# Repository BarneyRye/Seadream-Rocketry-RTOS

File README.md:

# Seadream Rocketry PCB and Code
 Kicad files include schematic, pcb, extra symbols, footprints 3d files and also the production files for JLCPCB </br>
 Included code written in Platform.io on VSCode, uses prebuilt libaries and freeRTOS, one task for sensor reading and audio, other task for writing to SD

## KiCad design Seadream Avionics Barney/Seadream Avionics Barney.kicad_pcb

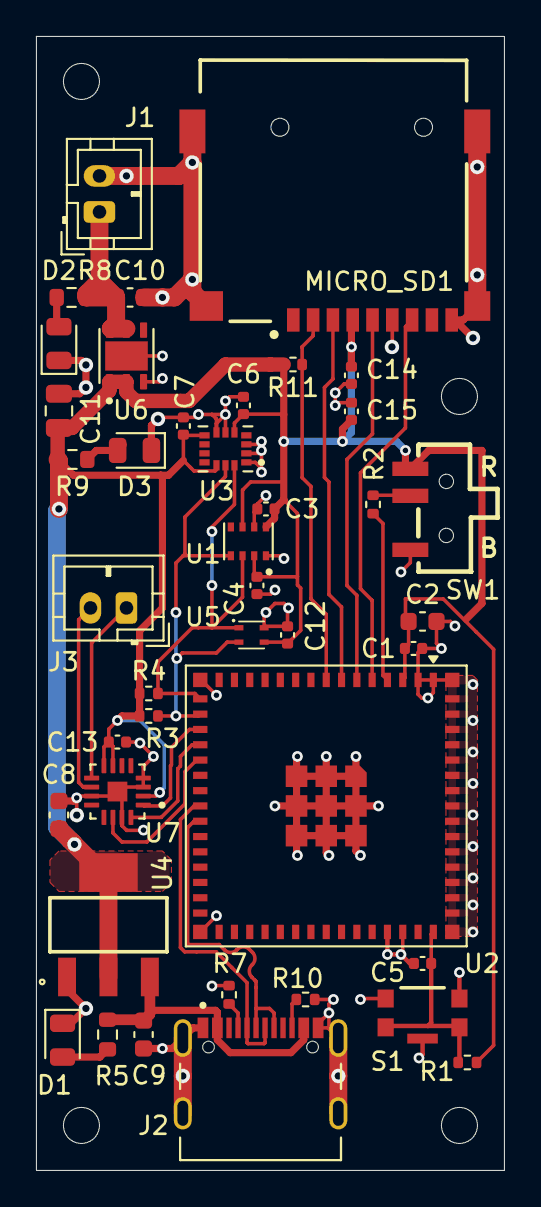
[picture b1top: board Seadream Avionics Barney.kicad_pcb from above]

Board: 2 copper layers, 26.0 x 63.0 mm, 41 parts (0 on the bottom side), 25 nets.

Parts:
C1, C3, C4, C5, C6, C7, C12, C13, C14: 100nF; C_0402_1005Metric
C2, C8, C9, C10: 10uF; C_0603_1608Metric
C11: 22uF; C_0805_2012Metric
C15: 1uF; C_0402_1005Metric
D1, D2, D3: LED; LED_0805_2012Metric
J1, J3: B2B-PH-K-S(LF)(SN); JST_PH_B2B-PH-K_1x02_P2.00mm_Vertical
J2: C393939; SHOUHAN_TYPE-C_16PIN_2MD__073_
MICRO_SD1: C91145; TF-01A
R1, R2, R11: 10k; R_0402_1005Metric
R3, R4: 4k7; R_0402_1005Metric
R5: 330; R_0603_1608Metric
R7, R10: 5k1; R_0402_1005Metric
R8, R9: 220; R_0603_1608Metric
S1: KMR221GLFS; SW_KMR221GLFS
SW1: SSSS810701; SW-SMD_SSSS810701
U1: BMP280; XDCR_BMP280
U2: ESP32-S3-MINI-1U-N8; ESP32-S2-MINI-1U
U3: LSM6DSO32TR; XDCR_LSM6DSO32TR
U4: LD1117S33TR; SOT230P700X180-4N
U5: SHT40-AD1B-R3; SHT4X
U6: LD39200PU33R; SON95P300X300X100-7N
U7: MAX98357AETE_T; QFN50P300X300X80-17N

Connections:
+3.3V: C1.2, C2.2, C3.1, C4.1, C6.1, C7.1, C8.1, C11.2, C12.1, C13.1, C14.2, C15.2, MICRO_SD1.4 (VDD), R1.2, R3.1, R4.1, R9.1, R11.1, SW1.3 (C), U1.2 (CSB), U1.6 (VDDIO), U1.8 (VDD), U2.3 (3V3), U3.5 (VDDIO), U3.8 (VDD), U3.12 (CS), U4.2 (OUT), U4.4 (OUT), U5.3 (VDD), U6.1 (OUT), U6.2 (SENSE), U7.2 (GAIN_SLOT), U7.7 (VDD), U7.8 (VDD)
/BOOT: R2.2, U2.4 (IO0)
/CD: MICRO_SD1.2 (CD/DAT3), R11.2, U2.8 (IO4)
/D+: J2.A6 (DP1), J2.B6 (DP2), U2.24 (IO20)
/D-: J2.A7 (DN1), J2.B7 (DN2), U2.23 (IO19)
/EN: C5.2, R1.1, S1.1, S1.4, U2.45 (EN)
/IO12: R4.2, U1.3 (SDI), U2.16 (IO12), U3.14 (SDA), U5.1 (SDA)
/IO13: R3.2, U1.4 (SCK), U2.17 (IO13), U3.13 (SCL), U5.2 (SCL)
/IO14: U2.18 (IO14), U7.1 (DIN)
/IO15: U2.19 (IO15), U7.16 (BCLK)
/IO16: U2.20 (IO16), U7.14 (LRCLK)
/MISO: MICRO_SD1.7 (DAT0), U2.5 (IO1)
/MOSI: MICRO_SD1.3 (CMD), U2.7 (IO3)
/OUT+: J3.1, U7.9 (OUTP)
/OUT-: J3.2, U7.10 (OUTN)
/SCK: MICRO_SD1.5 (CLK), U2.6 (IO2)
/USB 5V: C9.1, J2.A4_B9 (VBUS_A), J2.B4_A9 (VBUS_B), R5.1, U4.3 (IN)
GND: C1.1, C2.1, C3.2, C4.2, C5.1, C6.2, C7.2, C8.2, C9.2, C10.1, C11.1, C12.2, C13.2, C14.1, C15.1, D1.1 (K), D2.1 (K), D3.1 (K), J1.2, J2.A1_B12 (GND_A), J2.B1_A12 (GND_B), J2.SH1 (SHIELD), J2.SH2 (SHIELD), J2.SH3 (SHIELD), J2.SH4 (SHIELD), MICRO_SD1.6 (VSS), MICRO_SD1.CD1 (CD), MICRO_SD1.MP1 (SHIELD), MICRO_SD1.MP2 (SHIELD), MICRO_SD1.MP3 (SHIELD), MICRO_SD1.MP4 (SHIELD), R7.1, R10.2, S1.2, S1.3, S1.5, SW1.1 (A), U1.1 (GND), U1.7 (GND), U2.1 (GND1), U2.2 (GND1), U2.42 (GND1), U2.43 (GND1), U2.46 (GND1), U2.47 (GND1), U2.48 (GND1), U2.49 (GND1), U2.50 (GND1), U2.51 (GND1), U2.52 (GND1), U2.53 (GND1), U2.54 (GND2), U2.55 (GND2), U2.56 (GND2), U2.57 (GND2), U2.58 (GND2), U2.59 (GND2), U2.60 (GND3), U2.61, U2.62 (GND2), U2.63 (GND2), U2.64 (GND2), U2.65 (GND2), U3.1 (SDO/SA0), U3.2 (SDX), U3.3 (SCX), U3.6 (GND), U3.7 (GND), U4.1 (GND), U5.4 (VSS), U6.3 (GND), U6.7 (EXP), U7.3 (GND), U7.4 (SD_MODE), U7.11 (GND), U7.15 (GND), U7.17 (EP)
unnamed: D1.2 (A), R5.2
unnamed: D2.2 (A), R8.2
unnamed: D3.2 (A), R9.2
unnamed: C10.2, J1.1, R8.1, U6.5 (EN), U6.6 (IN)
unnamed: J2.A5 (CC1), R7.2
unnamed: J2.B5 (CC2), R10.1
unnamed: R2.1, SW1.2 (B)

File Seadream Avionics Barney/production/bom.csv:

"Reference","Qty","Value","DNP","Exclude from BOM","Exclude from Board","Footprint","Datasheet","Description","Part NO."
"C1,C3,C4,C5,C6,C7,C12,C13,C14","9","100nF","","","","Capacitor_SMD:C_0402_1005Metric","https://jlcpcb.com/api/file/downloadByFileSystemAccessId/857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","CL05B104KO5NNNC","C1525"
"C2,C8,C9,C10","4","10uF","","","","Capacitor_SMD:C_0603_1608Metric","https://jlcpcb.com/api/file/downloadByFileSystemAccessId/857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","CL10A106KP8NNNC","C19702"
"C11","1","22uF","","","","Capacitor_SMD:C_0805_2012Metric","https://jlcpcb.com/api/file/downloadByFileSystemAccessId/857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","CL21A226MAQNNNE","C45783"
"C15","1","1uF","","","","Capacitor_SMD:C_0402_1005Metric","https://jlcpcb.com/api/file/downloadByFileSystemAccessId/857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","CL05A105KA5NQNC","C52923"
"D1,D2,D3","3","LED","","","","LED_SMD:LED_0805_2012Metric","https://jlcpcb.com/api/file/downloadByFileSystemAccessId/855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","NCD0805R1","C84256"
"J1,J3","2","B2B-PH-K-S(LF)(SN)","","","","Connector_JST:JST_PH_B2B-PH-K_1x02_P2.00mm_Vertical","https://jlcpcb.com/api/file/downloadByFileSystemAccessId/858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","B2B-PH-K-S(LF)(SN)","C131337"
"J2","1","TYPE-C16PIN","","","","2FOOTPRINTS:SHOUHAN_TYPE-C_16PIN_2MD__073_","https://jlcpcb.com/api/file/downloadByFileSystemAccessId/858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","TYPE-C16PIN","C393939"
"MICRO_SD1","1","TF-01A","","","","2FOOTPRINTS:TF-01A","https://jlcpcb.com/api/file/downloadByFileSystemAccessId/858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","TF-01A","C91145"
"R1,R2,R11","3","10k","","","","Resistor_SMD:R_0402_1005Metric","https://jlcpcb.com/api/file/downloadByFileSystemAccessId/858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","0402WGJ0103TCE","C25531"
"R3,R4","2","4k7","","","","Resistor_SMD:R_0402_1005Metric","https://jlcpcb.com/api/file/downloadByFileSystemAccessId/857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","0402WGF4701TCE","C25900"
"R5","1","330","","","","Resistor_SMD:R_0603_1608Metric","https://jlcpcb.com/api/file/downloadByFileSystemAccessId/857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","0603WAF3300T5E","C23138"
"R7,R10","2","5k1","","","","Resistor_SMD:R_0402_1005Metric","https://jlcpcb.com/api/file/downloadByFileSystemAccessId/857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","0402WGF5101TCE","C25905"
"R8,R9","2","220","","","","Resistor_SMD:R_0603_1608Metric","https://jlcpcb.com/api/file/downloadByFileSystemAccessId/857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","0603WAF2200T5E","C22962"
"S1","1","KMR221GLFS","","","","2FOOTPRINTS:SW_KMR221GLFS","https://jlcpcb.com/api/file/downloadByFileSystemAccessId/858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","KMR221GLFS","C72443"
"SW1","1","SSSS810701","","","","2FOOTPRINTS:SW-SMD_SSSS810701","https://jlcpcb.com/api/file/downloadByFileSystemAccessId/858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","SSSS810701","C97433"
"U1","1","BMP280","","","","2FOOTPRINTS:XDCR_BMP280","https://jlcpcb.com/api/file/downloadByFileSystemAccessId/858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","BMP280","C83291"
"U2","1","ESP32-S3-MINI-1U-N8","","","","RF_Module:ESP32-S2-MINI-1U","https://documentation.espressif.com/esp32-s3-mini-1_mini-1u_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","ESP32-S3-MINI-1U-N8","C2980299"
"U3","1","LSM6DSO32TR","","","","2FOOTPRINTS:XDCR_LSM6DSO32TR","https://jlcpcb.com/api/file/downloadByFileSystemAccessId/858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","LSM6DSO32TR","C1864162"
"U4","1","LD1117S33TR","","","","2FOOTPRINTS:SOT230P700X180-4N","https://jlcpcb.com/api/file/downloadByFileSystemAccessId/858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","LD1117S33TR","C86781"
"U5","1","SHT40-AD1B-R3","","","","2FOOTPRINTS:SHT4X","https://jlcpcb.com/api/file/downloadByFileSystemAccessId/858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","SHT40-AD1B-R3","C2848306"
"U6","1","LD39200PU33R","","","","2FOOTPRINTS:SON95P300X300X100-7N","https://jlcpcb.com/api/file/downloadByFileSystemAccessId/858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","LD39200PU33R","C222192"
"U7","1","MAX98357AETE_T","","","","2FOOTPRINTS:QFN50P300X300X80-17N","https://jlcpcb.com/api/file/downloadByFileSystemAccessId/858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","MAX98357AETE_T","C910544"

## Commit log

2025-12-30 First code upload
2025-12-30 Test
2026-01-12 "Quick Edit"
2026-01-12 Added takeoff detection
2026-01-12 Edited so Serial prints over USB rather than UART
2026-01-12 Changed BMP180 for BMP280, and added calibration settings to BMP and IMU
2026-01-14 Changed I2C Speed
2026-01-18 Added more info to BOM for JLCPCB PCBA
2026-01-18 Changed file names
2026-01-19 Added logo
2026-01-20 File reorganise
2026-01-27 Added connection flags to sensors
2026-01-27 Quick fix
2026-02-04 Added apogee detection
2026-02-05 Added landing detection
2026-02-07 Changed song filename
2026-02-09 Changed reduce log rate to after apogee
2026-02-11 Quick edit
